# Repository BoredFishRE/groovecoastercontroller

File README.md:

# Groove Coaster Controller 2023 (Modified by Anthony Raudino)
This is a fork of the fork of the original project modified with some adjustments as well as acrylic cuts, custom prints as well as a custom PCB!

# This is a WIP as I refine things. Don't use the stick tubes from the CAD, they didn't convert well.

# WARNING!!! On the PCB, ground for the joysticks is pin 5, the pin on the connector all the way to the right. Your joystick may come with ground as pin 1, please make note of this.

* Original readme included in seperate file for anyone wanting to follow the original Teensy instructions, though I don't suggest it.

# Groove Coaster Controller
GrooveCoaster Controller replica with dimensions from real cabinet  
Box is 20 x 10 x 56.5 cm

# needed
- Microcontroller with an RP2040 (PCB is for sparkfun promicro 2040)
- a 3D printer
- a laser cutting machine
- 5mm plywood OR acrylic 
- 2 x seimitsu LS32-SE joysticks
- 2 x 60mm buttons
- A lot of screws, specific amount coming soon
- M3 heat set inserts, I suggest the CNC Kitchen since that's what I designed for.

# not needed, but suggested
 - 20g Sanwa springs (you need 2, but you can get a 10 pack easily)
 - 100g Omron V-10-1A4 x2 (for the 2 main buttons, you can get 3 if you want it on the start button, but you don't need it)

# things to 3d print
- 2 x joy_stick.stl
- 2 x joy_base.stl
- 2 x joy_tube.stl
- All the corner brackets. This will help in rigidity and assembly

# things to laser cut
- 2 x box_side.dxf
- 2 x box_insert.dxf (goes on box_middle, helps for rigidity)
- 1 x box_front.dxf
- 1 x box_back.dxf
- 1 x box_top.dxf
- 1 x box_middle.dxf
- 1 x box_bottom.dxf

# assembly
### COMING SOON

# soldering (If you're not using the PCB)
- Use schematic tbh.

# Firmware
- I will release soon, but I will be using GP2040-CE

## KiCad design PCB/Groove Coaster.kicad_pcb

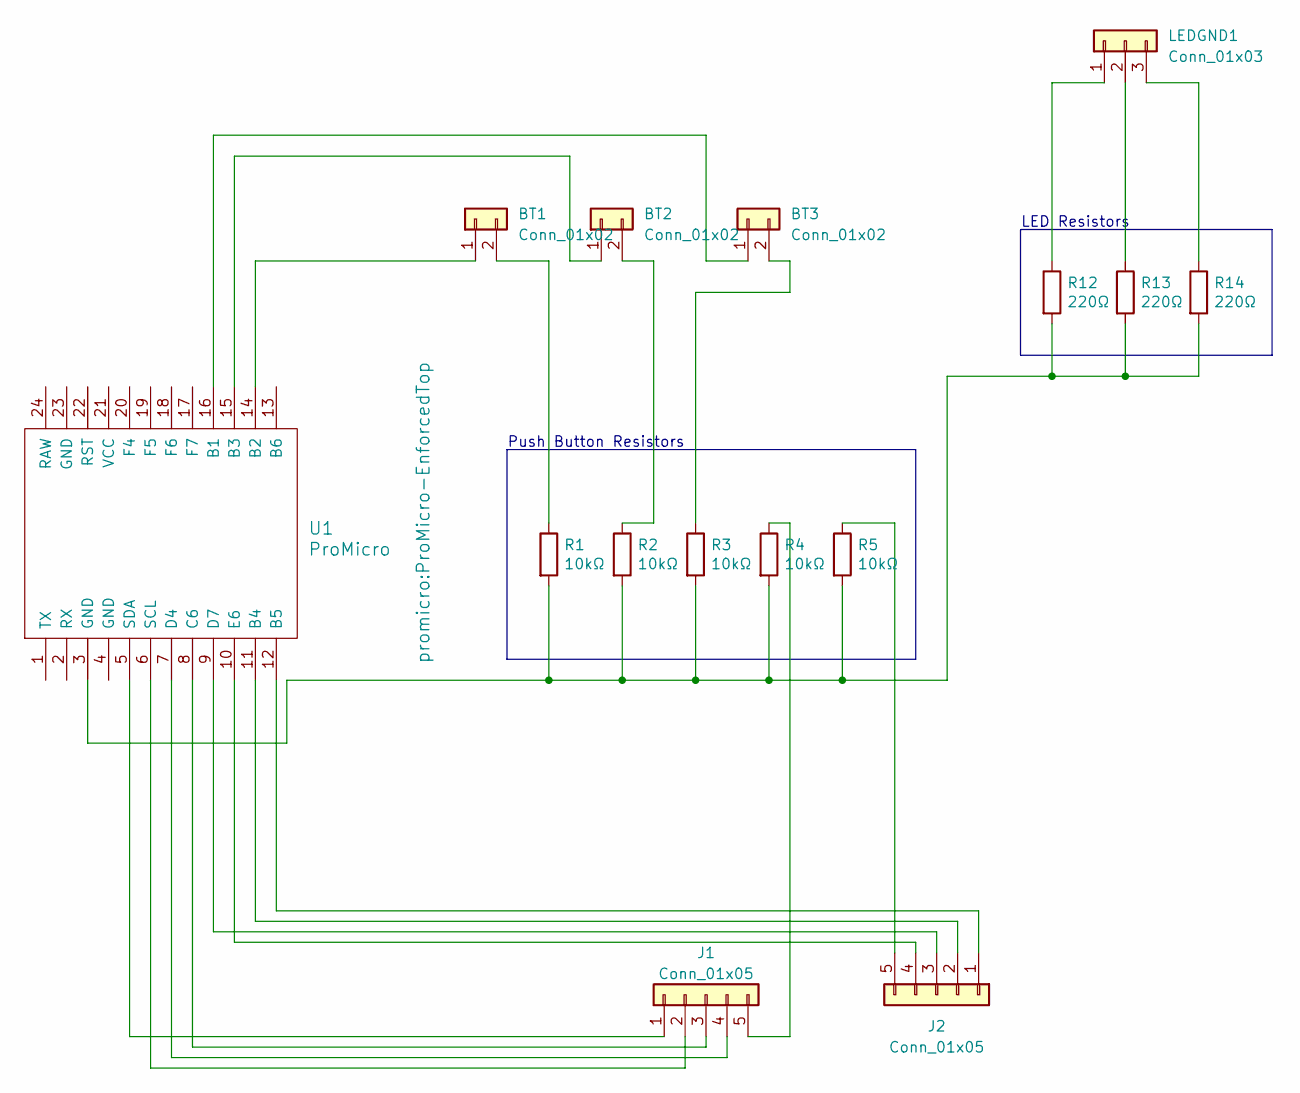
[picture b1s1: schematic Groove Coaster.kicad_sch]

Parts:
BT1, BT2, BT3: Conn_01x02; JST_XH_B2B-XH-A_1x02_P2.50mm_Vertical
J1, J2: Conn_01x05; JST_XH_B5B-XH-AM_1x05_P2.50mm_Vertical
LEDGND1: Conn_01x03; JST_XH_B3B-XH-A_1x03_P2.50mm_Vertical
R1, R2, R3, R4, R5: 10kΩ; R_1206_3216Metric
R12, R13, R14: 220Ω; R_1206_3216Metric
U1: ProMicro; ProMicro-EnforcedTop

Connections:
unnamed: BT1.1, U1.14 (B2)
unnamed: BT1.2, R1.1
unnamed: BT2.1, U1.15 (B3)
unnamed: BT2.2, R2.1
unnamed: BT3.1, U1.16 (B1)
unnamed: BT3.2, R3.1
unnamed: J1.1, U1.5 (SDA)
unnamed: J1.2, U1.6 (SCL)
unnamed: J1.3, U1.8 (C6)
unnamed: J1.4, U1.7 (D4)
unnamed: J1.5, R4.1
unnamed: J2.1, U1.12 (B5)
unnamed: J2.2, U1.11 (B4)
unnamed: J2.3, U1.9 (D7)
unnamed: J2.4, U1.10 (E6)
unnamed: J2.5, R5.1
unnamed: LEDGND1.1, R12.1
unnamed: LEDGND1.2, R13.1
unnamed: LEDGND1.3, R14.1
unnamed: R1.2, R2.2, R3.2, R4.2, R5.2, R12.2, R13.2, R14.2, U1.3 (GND)

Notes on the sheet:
LED Resistors
Push Button Resistors

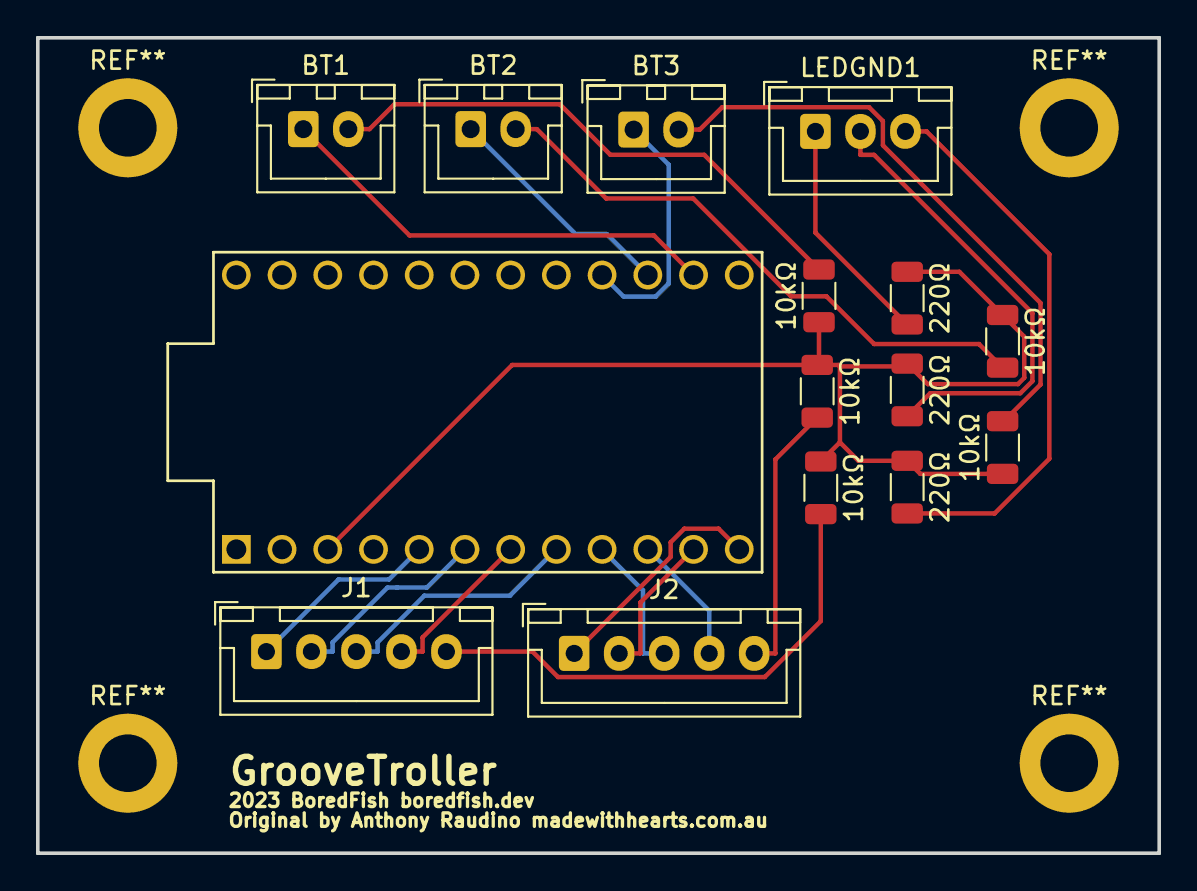
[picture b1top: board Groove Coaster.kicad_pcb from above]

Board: 2 copper layers, 62.3 x 45.3 mm, 15 parts (0 on the bottom side), 20 nets.

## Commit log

2021-09-13 lets G R O O O O O O V E C O A S T E R
    added crab vector art
2021-09-13 cleaned up project
2021-09-13 + Artwork Folder
2021-09-14 Updated artwork
2021-09-14 Removed mac file junk
2021-09-19 added reference photos
2021-09-20 created single file cut layout and panel with USB C port hole
2021-09-22 pcb things
2021-09-29 rebuilt box in 6mm in fusion 360 and created 6mm compatible laser cut files
2021-09-29 renamed cad image
2021-10-03 added square button hole
2023-09-08 let's go
2023-09-08 All da changes
2023-09-22 oopies
2024-07-13 pcbdeeznutz
2024-07-20 Fix Base Ring
    old prevented diagonal movements from working so this one fixes that issue.
2024-07-20 GP2040CE config
    oops forgor to do this
